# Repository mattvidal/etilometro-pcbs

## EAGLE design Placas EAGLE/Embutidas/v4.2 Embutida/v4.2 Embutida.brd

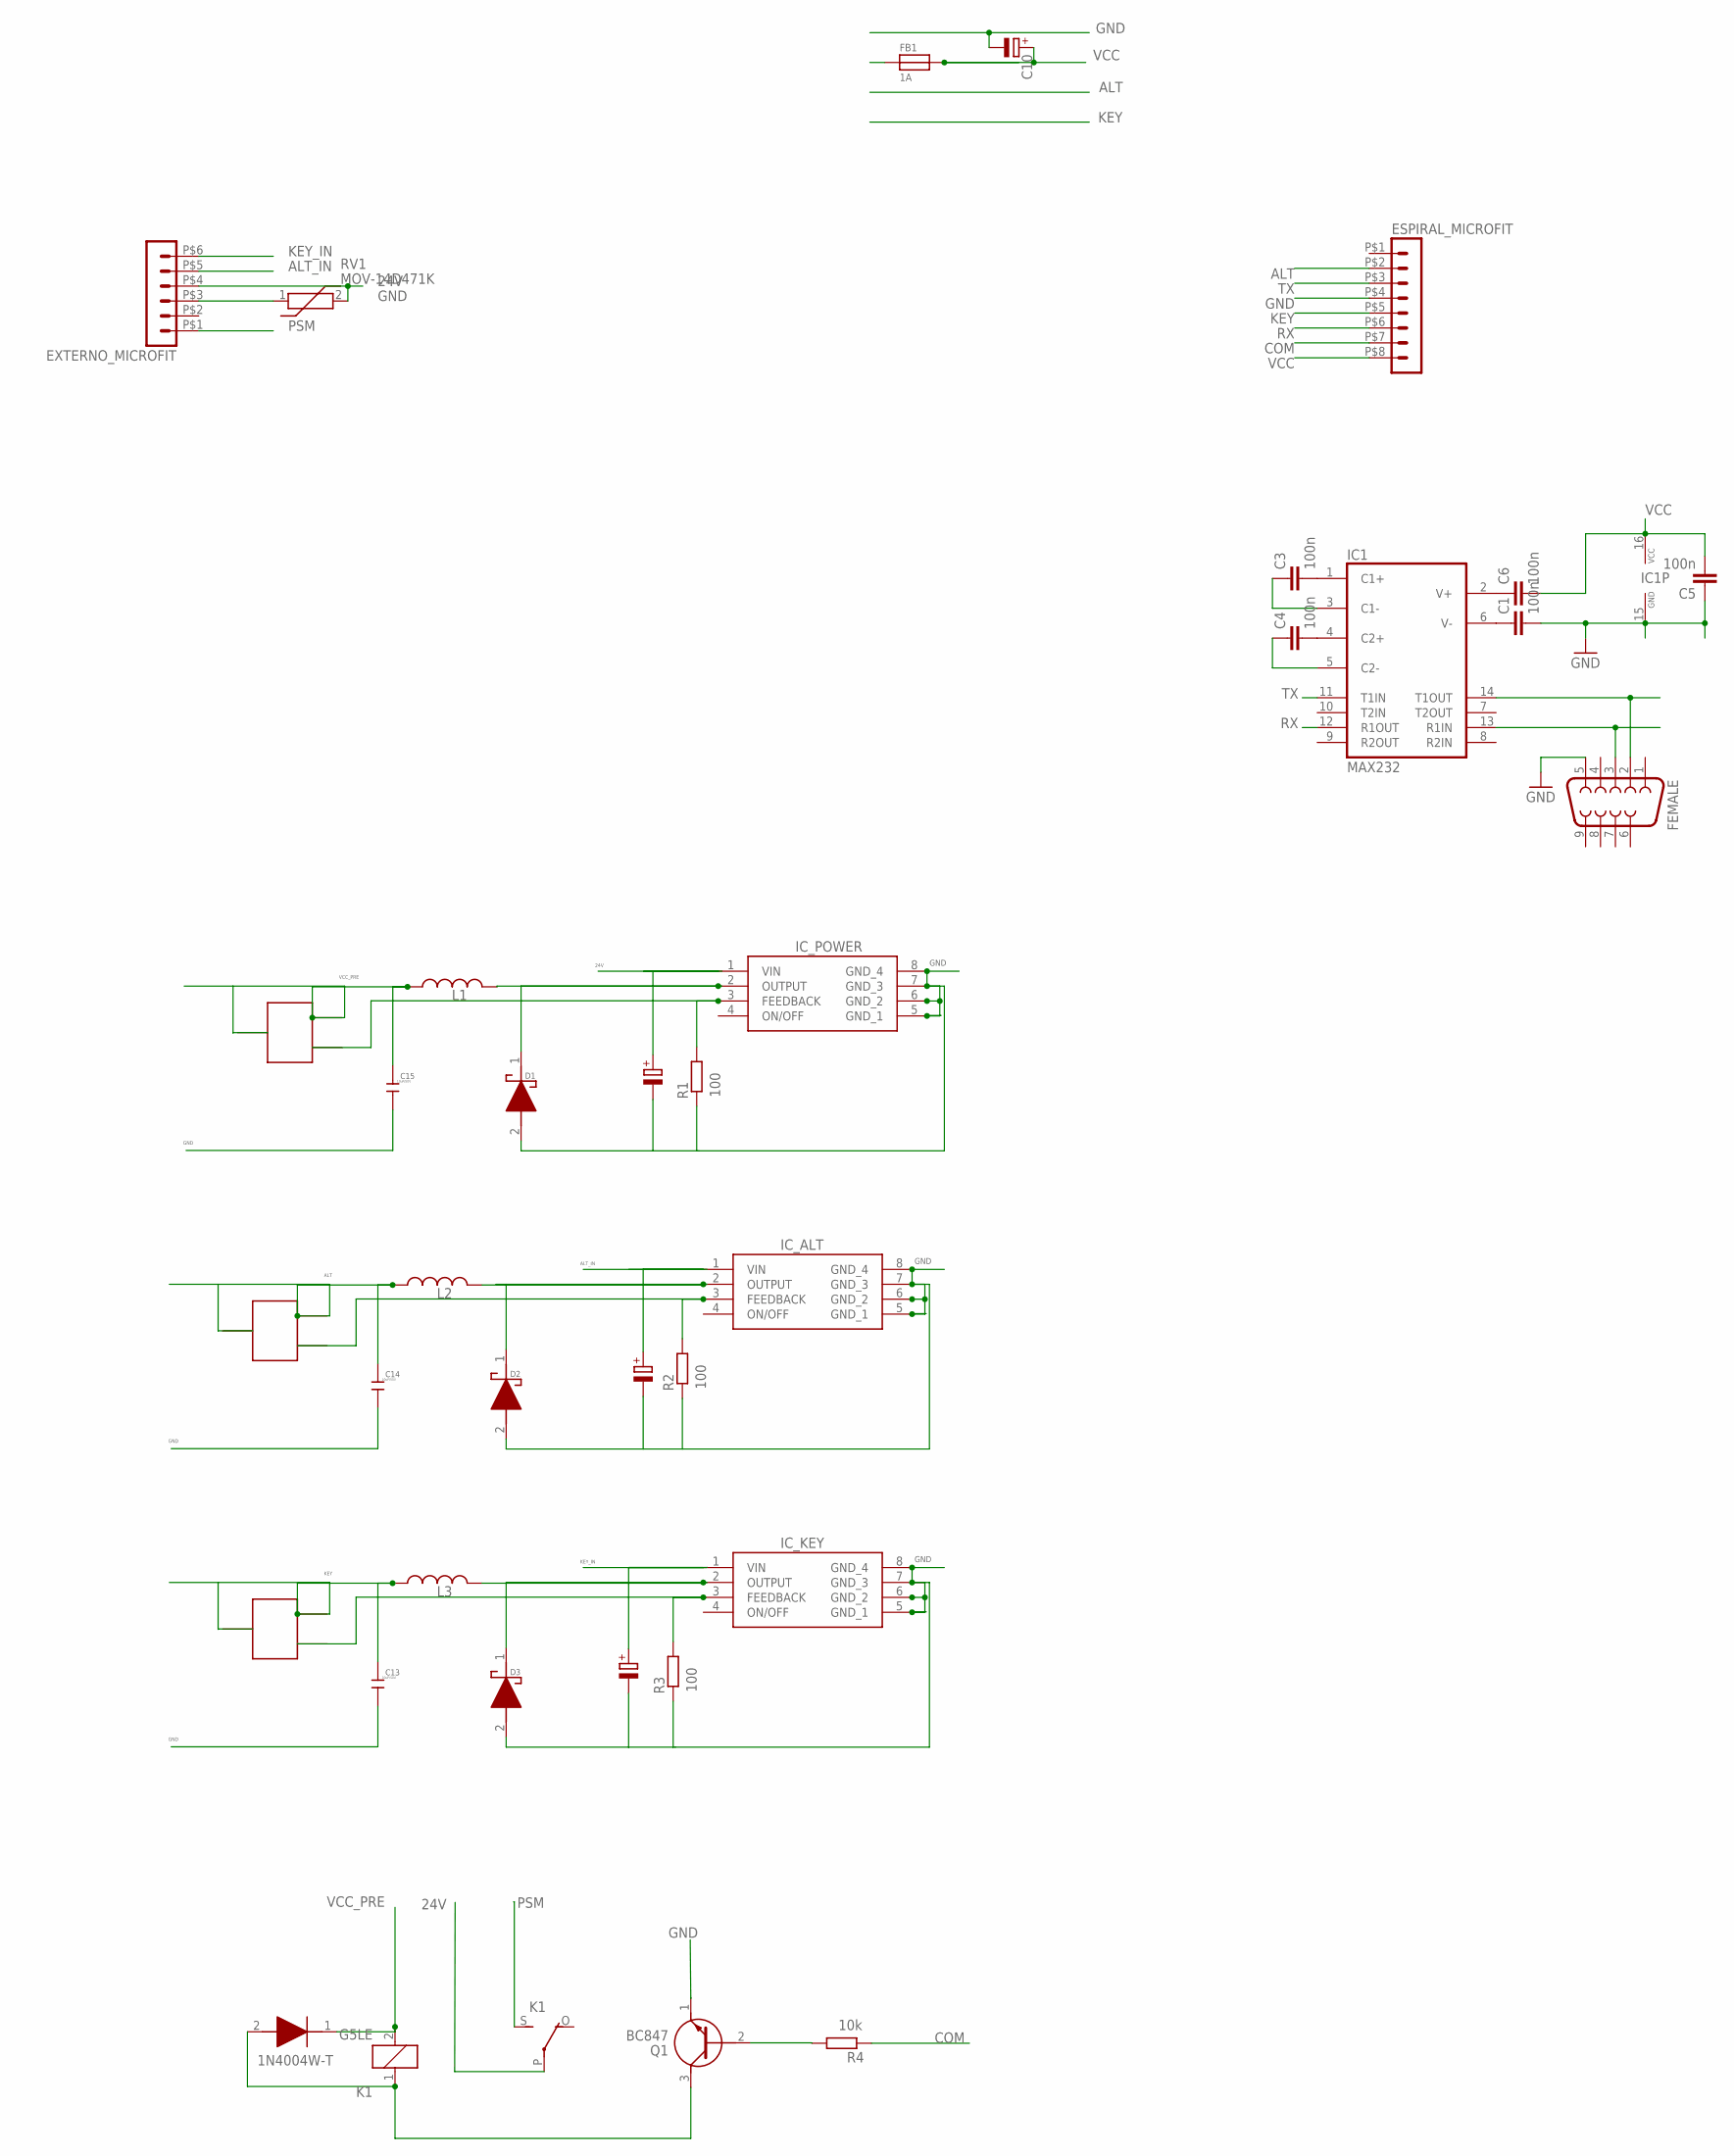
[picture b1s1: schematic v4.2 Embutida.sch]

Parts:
C1, C3, C4, C5, C6: 100n; C0805; MPN C0805C104K8RACAUTO
C2: 22uF/50v; PANASONIC_D; MPN EEH-ZA1H220P
C8, C9: 22uF/50V; PANASONIC_D; MPN EEH-ZA1H220P
C10: CPOL-EUB45181C; B45181C
C13, C14, C15: 10uF/50V; C0805; MPN C2012X5R1H106K125AC
D1, D2, D3: 1N5819HW1-7-F; SODFL3518X115N; MPN 1N5822 SS34
D5: 1N4004W-T; SODFL3818X130N
ESPIRAL_MICROFIT: HEADER_POS8_43045-0800; 43045-0800; MPN 43045-0800
EXTERNO_MICROFIT: HEADER_POS6_43045-0600; 43045-0600; MPN 43045-0600
FB1: 1A; 0805; MPN BLM21AG121SN1D
FEMALE: F09H; MPN FEMALE DR9
IC1: MAX232; SO16; MPN MAX3232CSE+
IC_ALT: XL1509-3.3E1; SOIC127P600X175-8N; MPN XL1509-ADJE1
IC_KEY: XL1509-3.3E1; SOIC127P600X175-8N; MPN XL1509-ADJE1
IC_POWER: XL1509-3.3E1; SOIC127P600X175-8N; MPN XL1509-ADJE1
K1: G5LE
L1, L2, L3: 47uH; SDE0604A-470M; MPN SDE0604A-470M
Q1: BC847
R1, R2, R3: 100; R0805; MPN RA73F2A100RBTDF
R4: 10k; R0805; MPN RA73F2A100RBTDF
RV1: MOV-14D471K; MOV14D471K
T1, T2, T3: TRIMPOT 10K; TRIMPOT; MPN EVM3ESX50B14

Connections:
24V: C2.+, EXTERNO_MICROFIT.P$4 (4), IC_POWER.1 (VIN), K1.P, RV1.2
ALT: C14.2, ESPIRAL_MICROFIT.P$2 (2), L2.1, T2.VCC1, T2.VCC2
ALT_IN: C8.+, EXTERNO_MICROFIT.P$5 (5), IC_ALT.1 (VIN)
COM: ESPIRAL_MICROFIT.P$7 (7), R4.1
GND: C1.2, C2.-, C5.1, C8.-, C9.-, C10.-, C13.1, C14.1, C15.1, D1.2 (A), D2.2 (A), D3.2 (A), ESPIRAL_MICROFIT.P$4 (4), EXTERNO_MICROFIT.P$3 (3), FEMALE.5, IC1.15 (GND), IC_ALT.5 (GND_1), IC_ALT.6 (GND_2), IC_ALT.7 (GND_3), IC_ALT.8 (GND_4), IC_KEY.5 (GND_1), IC_KEY.6 (GND_2), IC_KEY.7 (GND_3), IC_KEY.8 (GND_4), IC_POWER.5 (GND_1), IC_POWER.6 (GND_2), IC_POWER.7 (GND_3), IC_POWER.8 (GND_4), Q1.1 (E), R1.1, R2.1, R3.1, RV1.1
KEY: C13.2, ESPIRAL_MICROFIT.P$5 (5), L3.1, T3.VCC1, T3.VCC2
KEY_IN: C9.+, EXTERNO_MICROFIT.P$6 (6), IC_KEY.1 (VIN)
unnamed: D1.1 (K), IC_POWER.2 (OUTPUT), L1.2
unnamed: D2.1 (K), IC_ALT.2 (OUTPUT), L2.2
unnamed: IC_ALT.3 (FEEDBACK), R2.2, T2.OUT
unnamed: D3.1 (K), IC_KEY.2 (OUTPUT), L3.2
unnamed: IC_KEY.3 (FEEDBACK), R3.2, T3.OUT
unnamed: D5.2 (A), K1.1, Q1.3 (C)
unnamed: IC_POWER.3 (FEEDBACK), R1.2, T1.OUT
unnamed: Q1.2 (B), R4.2
unnamed: C3.2, IC1.1 (C1+)
unnamed: C4.2, IC1.4 (C2+)
unnamed: C3.1, IC1.3 (C1-)
unnamed: C4.1, IC1.5 (C2-)
unnamed: C6.1, IC1.2 (V+)
unnamed: C1.1, IC1.6 (V-)
unnamed: FEMALE.2, IC1.14 (T1OUT)
unnamed: FEMALE.3, IC1.13 (R1IN)
PSM: EXTERNO_MICROFIT.P$1 (1), K1.S
RX: ESPIRAL_MICROFIT.P$6 (6), IC1.12 (R1OUT)
TX: ESPIRAL_MICROFIT.P$3 (3), IC1.11 (T1IN)
VCC: C5.2, C6.2, C10.+, ESPIRAL_MICROFIT.P$8 (8), FB1.2, IC1.16 (VCC)
VCC_PRE: C15.2, D5.1 (K), FB1.1, K1.2, L1.1, T1.VCC1, T1.VCC2

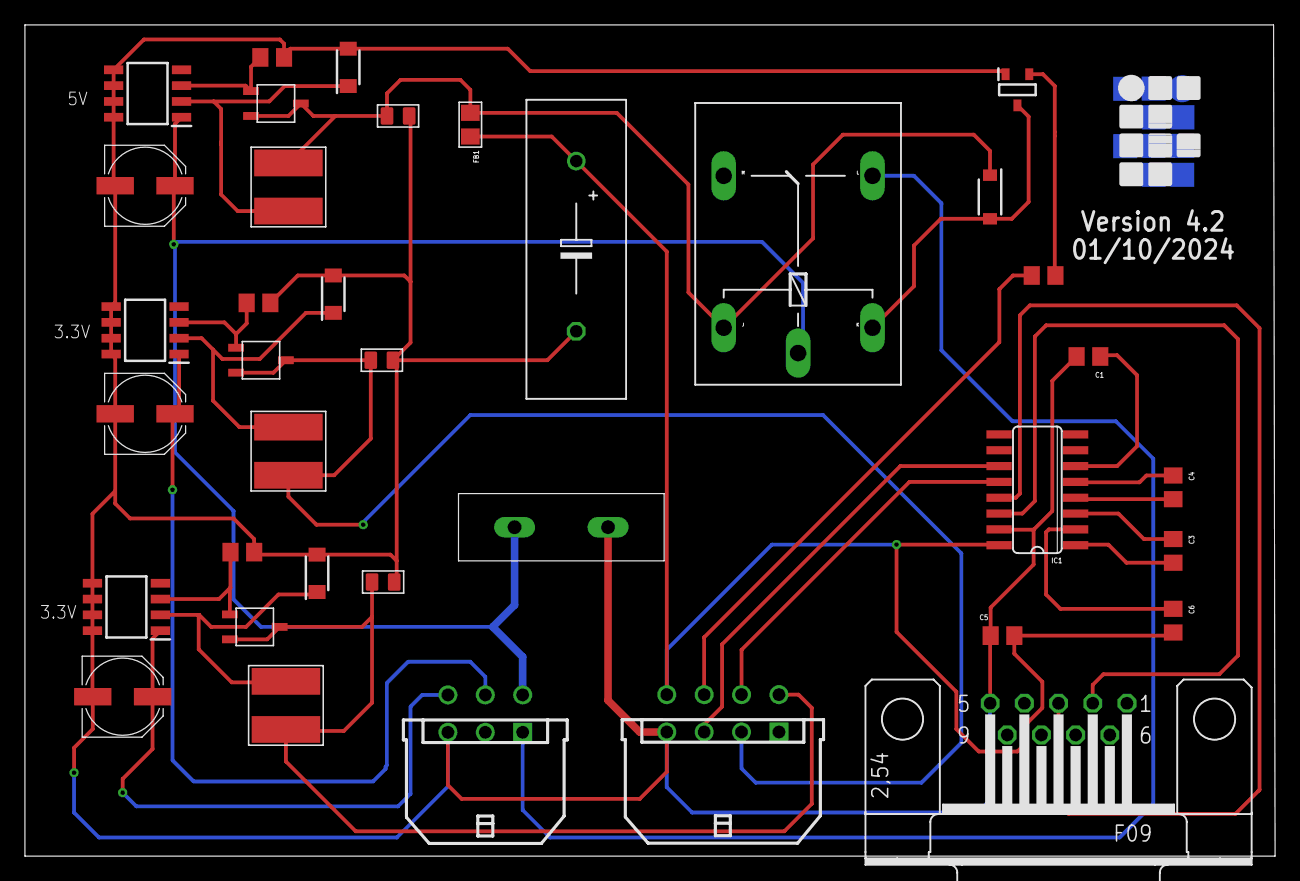
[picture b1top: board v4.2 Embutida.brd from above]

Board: 2 copper layers, 100.3 x 66.7 mm, 37 parts (0 on the bottom side), 28 nets.

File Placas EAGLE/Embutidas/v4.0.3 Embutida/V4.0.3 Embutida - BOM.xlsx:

Part | Value | MPN
C1 | 100n | C0805C104K8RACAUTO
C2 | 22uF/50v | EEH-ZA1H220P
C3 | 100n | C0805C104K8RACAUTO
C4 | 100n | C0805C104K8RACAUTO
C5 | 100n | C0805C104K8RACAUTO
C6 | 100n | C0805C104K8RACAUTO
C8 | 22uF/50V | EEH-ZA1H220P
C9 | 22uF/50V | EEH-ZA1H220P
C10 | 2200 uF | EEV-FK1A222Q
C13 | 10uF/50V | C2012X5R1H106K125AC
C14 | 10uF/50V | C2012X5R1H106K125AC
C15 | 10uF/50V | C2012X5R1H106K125AC
D1 | 1N5819HW1-7-F | 1N5822 SS34
D2 | 1N5819HW1-7-F | 1N5822 SS34
D3 | 1N5819HW1-7-F | 1N5822 SS34
D5 |  | 1N4004W-T
ESPIRAL_MICROFIT |  | 43045-0800
EXTERNO_MICROFIT |  | 43045-0600
FB1 | 1A | BLM21AG121SN1D
FEMALE |  | FEMALE DR9
IC1 | MAX232 | MAX3232CSE+
IC_ALT | XL1509-3.3E1 | XL1509-ADJE1
IC_KEY | XL1509-3.3E1 | XL1509-ADJE1
IC_POWER | XL1509-3.3E1 | XL1509-ADJE1
K1 |  | G5LE
L1 | 47uH | SDE0604A-470M
L2 | 47uH | SDE0604A-470M
L3 | 47uH | SDE0604A-470M
Q1 |  | BC847
R1 | 100 | RA73F2A100RBTDF
R2 | 100 | RA73F2A100RBTDF
R3 | 100 | RA73F2A100RBTDF
R4 | 10k | RA73F2A100RBTDF
T1 | TRIMPOT 10K | EVM3ESX50B14
T2 | TRIMPOT 10K | EVM3ESX50B14
T3 | TRIMPOT 10K | EVM3ESX50B14

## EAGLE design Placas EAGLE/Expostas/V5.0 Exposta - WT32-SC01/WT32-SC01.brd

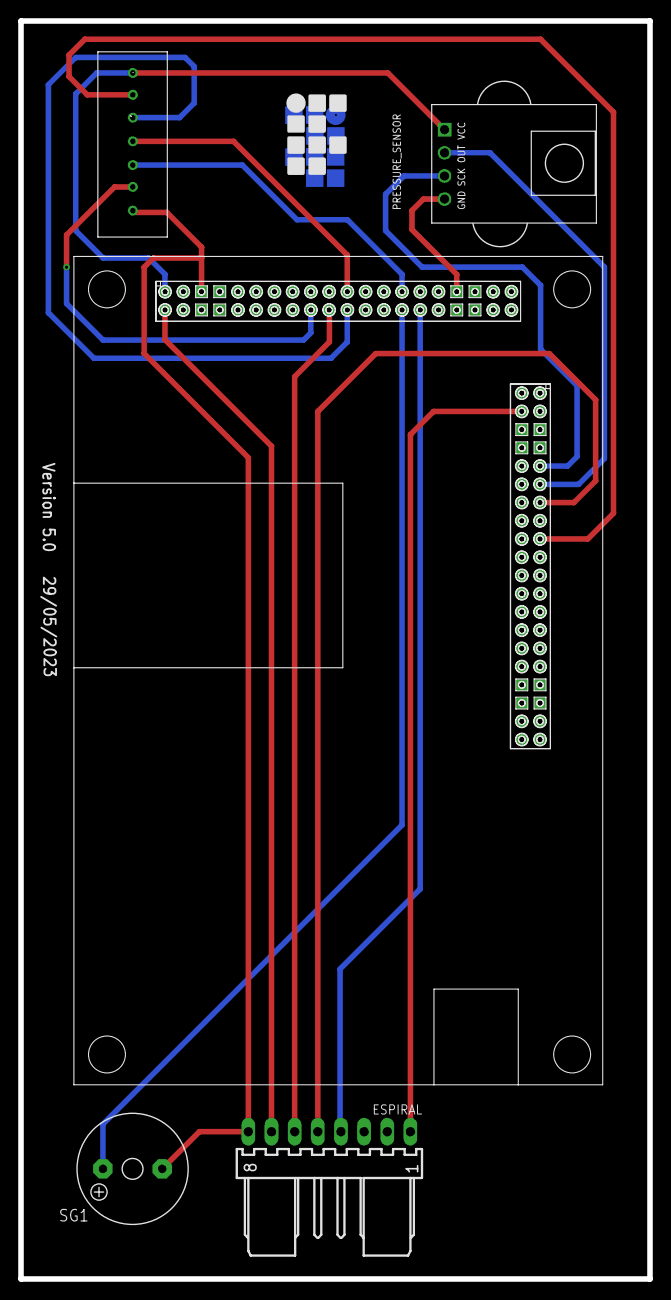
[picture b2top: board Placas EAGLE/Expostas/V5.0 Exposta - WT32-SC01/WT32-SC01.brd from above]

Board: 2 copper layers, 69.0 x 138.0 mm, 5 parts (0 on the bottom side), 14 nets.

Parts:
ESPIRAL: Espiral; 7395-08
PRESSURE_SENSOR: PRESSURE_SENSORWITH_SMDPADS&THROUGHHOLES; MPS20N0040D
SG1: F/QMX
U$1: SENSOR
U$2: WT32_SC01; WT32

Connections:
3V3: ESPIRAL.1, U$2.3V3_3, U$2.3V3_4, U$2.3V3_5, U$2.3V3_6
5V: ESPIRAL.7, PRESSURE_SENSOR.VCC, U$1.VCC, U$2.5V, U$2.5V_2, U$2.5V_3, U$2.5V_4, U$2.5V_5, U$2.5V_6, U$2.5V_7, U$2.5V_8
GND: ESPIRAL.8, PRESSURE_SENSOR.GND, SG1.-, U$1.GND, U$2.GND, U$2.GND_2, U$2.GND_3, U$2.GND_4, U$2.GND_5, U$2.GND_6, U$2.GND_7, U$2.GND_8, U$2.GND_9, U$2.GND_10, U$2.GND_11, U$2.GND_12, U$2.GND_13, U$2.GND_14, U$2.P$7, U$2.P$8
IO0: U$1.HEAT, U$2.IO0, U$2.IO0_2
IO22: U$1.SCL, U$2.IO22, U$2.IO22_2
IO32: PRESSURE_SENSOR.OUT, U$2.IO32, U$2.IO32_2
IO33: PRESSURE_SENSOR.SCK, U$2.IO33, U$2.IO33_2
unnamed: ESPIRAL.6, U$2.IO23_2
unnamed: ESPIRAL.4, U$2.IO2_2
unnamed: U$1.A_OUT, U$2.IO34_2
unnamed: U$1.SDA, U$2.IO21_2
unnamed: U$1.WR, U$2.IO12
unnamed: SG1.+, U$2.IO15_2
unnamed: ESPIRAL.5, U$2.IO27

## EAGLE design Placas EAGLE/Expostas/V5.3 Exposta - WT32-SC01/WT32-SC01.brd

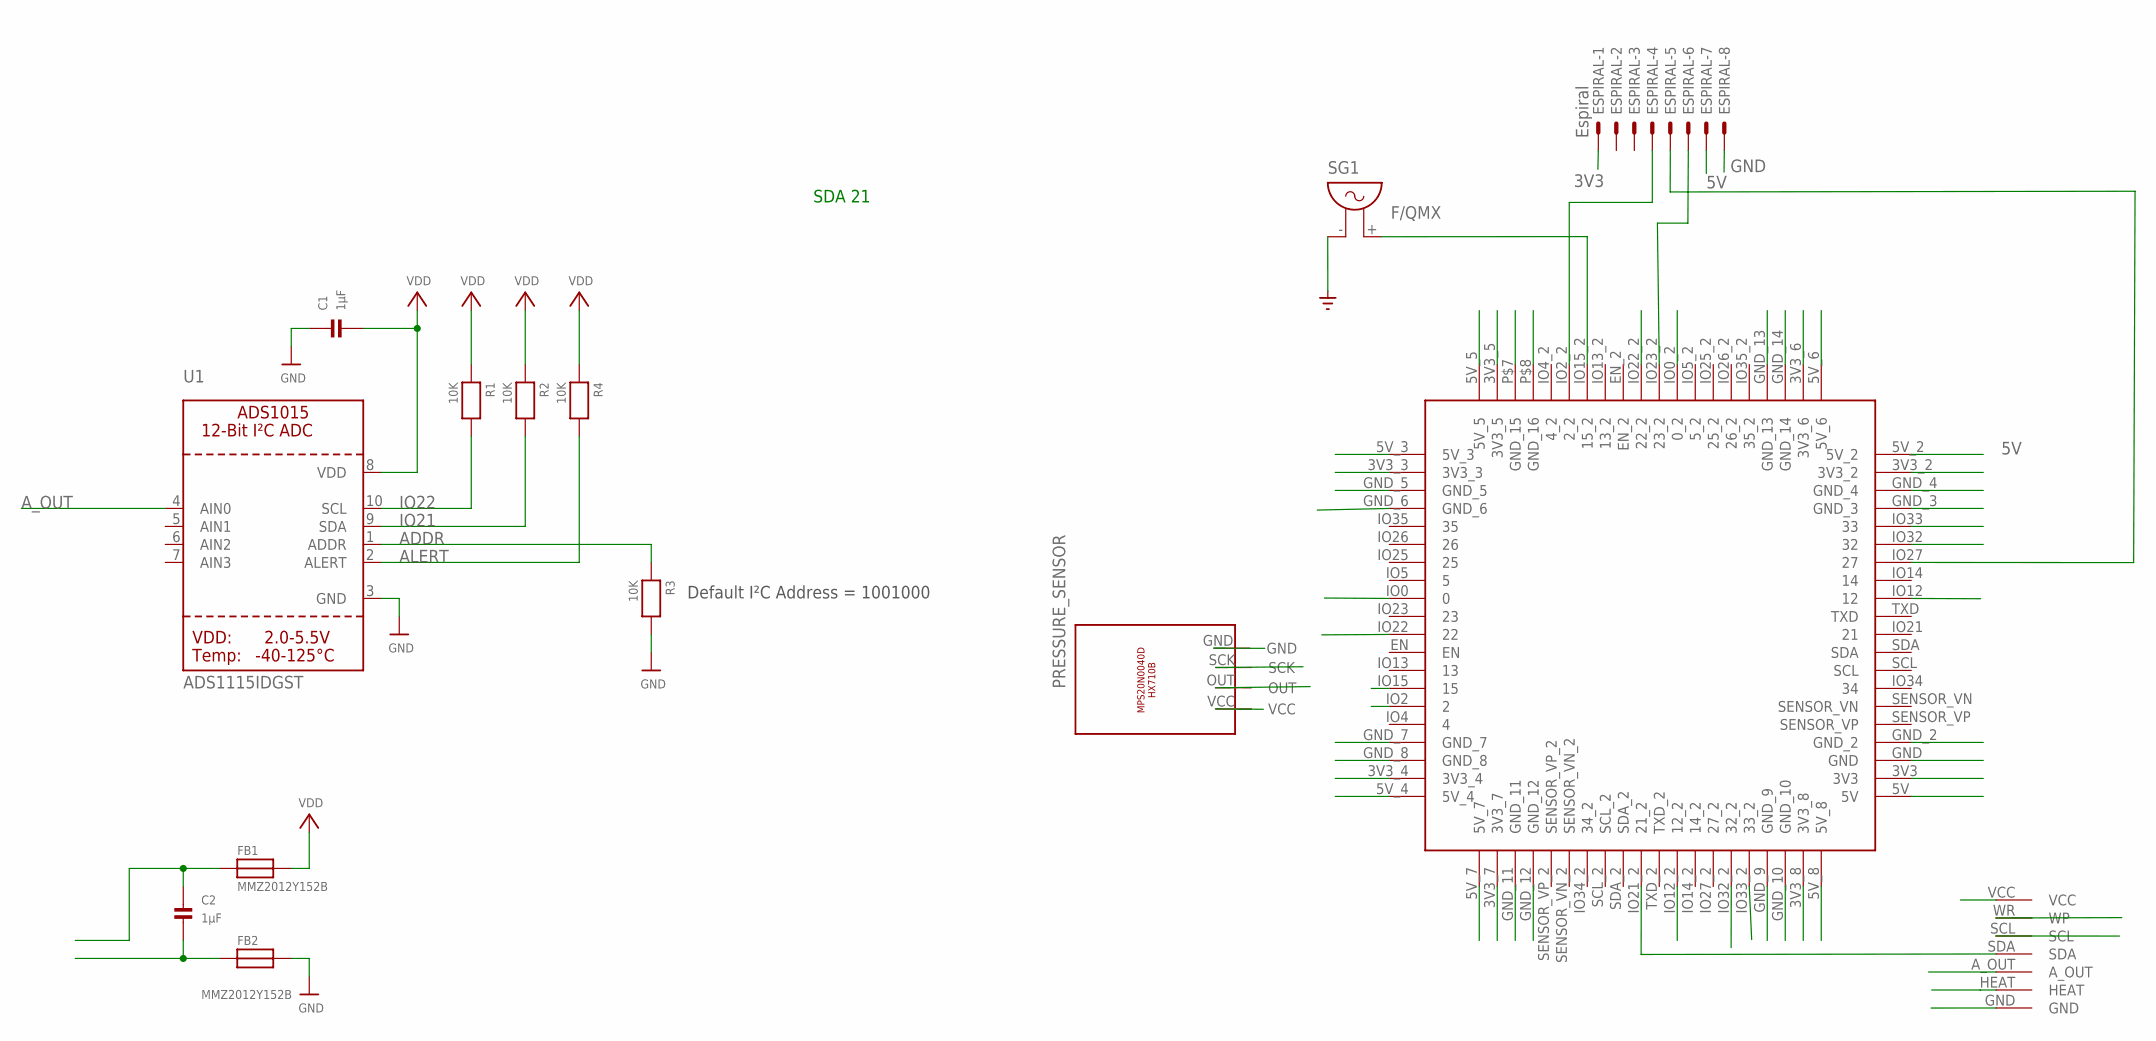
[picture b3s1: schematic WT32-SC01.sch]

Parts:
C1, C2: 1µF; 0805
ESPIRAL: Espiral; 7395-08
FB1, FB2: MMZ2012Y152B; 0805
PRESSURE_SENSOR: PRESSURE_SENSORWITH_SMDPADS&THROUGHHOLES; MPS20N0040D
R1, R2, R3, R4: 10K; 0805
SG1: F/QMX
U1: ADS1115IDGST; MSOP10
U$1: SENSOR
U$2: WT32_SC01; WT32

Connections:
3V3: ESPIRAL.1, U$2.3V3, U$2.3V3_2, U$2.3V3_3, U$2.3V3_4, U$2.3V3_5, U$2.3V3_6
5V: ESPIRAL.7, FB1.2, PRESSURE_SENSOR.VCC, U$1.VCC, U$2.5V, U$2.5V_2, U$2.5V_3, U$2.5V_4, U$2.5V_5, U$2.5V_6, U$2.5V_7, U$2.5V_8
ADDR: R3.1, U1.1 (ADDR)
ALERT: R4.2, U1.2 (ALERT)
A_OUT: U1.4 (AIN0), U$1.A_OUT
GND: C1.1, ESPIRAL.8, FB2.2, PRESSURE_SENSOR.GND, R3.2, SG1.- (1), U1.3 (GND), U$1.GND, U$2.GND, U$2.GND_2, U$2.GND_3, U$2.GND_4, U$2.GND_5, U$2.GND_6, U$2.GND_7, U$2.GND_8, U$2.GND_9, U$2.GND_10, U$2.GND_11, U$2.GND_12, U$2.GND_13, U$2.GND_14, U$2.P$7 (GND_15), U$2.P$8 (GND_16)
IO0: U$1.HEAT, U$2.IO0 (0), U$2.IO0_2 (0_2)
IO2: ESPIRAL.4, U$2.IO2 (2), U$2.IO2_2 (2_2)
IO12: U$1.WR (WP), U$2.IO12 (12), U$2.IO12_2 (12_2)
IO15: SG1.+ (2), U$2.IO15 (15), U$2.IO15_2 (15_2)
IO21: R2.2, U1.9 (SDA), U$1.SDA, U$2.IO21_2 (21_2)
IO22: R1.2, U1.10 (SCL), U$1.SCL, U$2.IO22 (22), U$2.IO22_2 (22_2)
IO32: PRESSURE_SENSOR.OUT, U$2.IO32 (32), U$2.IO32_2 (32_2)
IO33: PRESSURE_SENSOR.SCK, U$2.IO33 (33), U$2.IO33_2 (33_2)
unnamed: ESPIRAL.6, U$2.IO23_2 (23_2)
unnamed: C2.2, FB2.1
unnamed: C2.1, FB1.1
unnamed: ESPIRAL.5, U$2.IO27 (27)
VDD: C1.2, R1.1, R2.1, R4.1, U1.8 (VDD)

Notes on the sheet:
Default I²C Address = 1001000
SDA 21

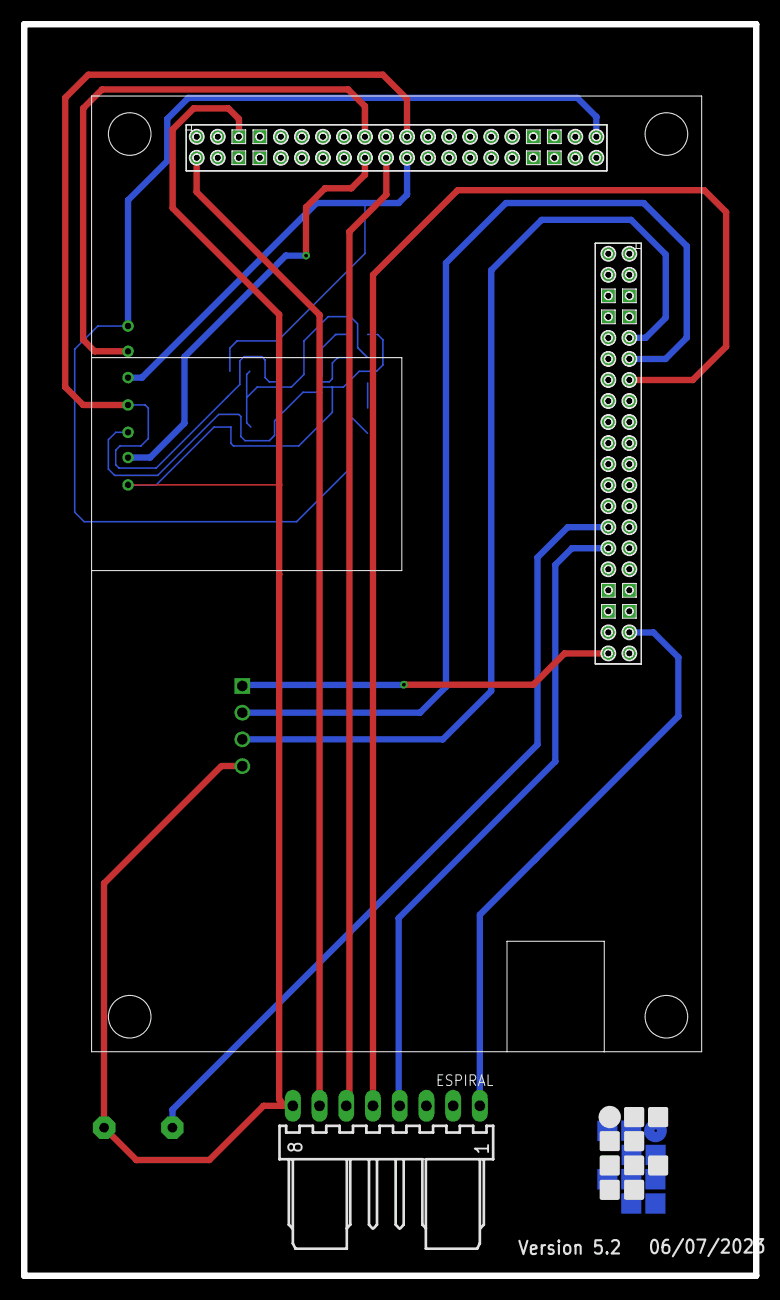
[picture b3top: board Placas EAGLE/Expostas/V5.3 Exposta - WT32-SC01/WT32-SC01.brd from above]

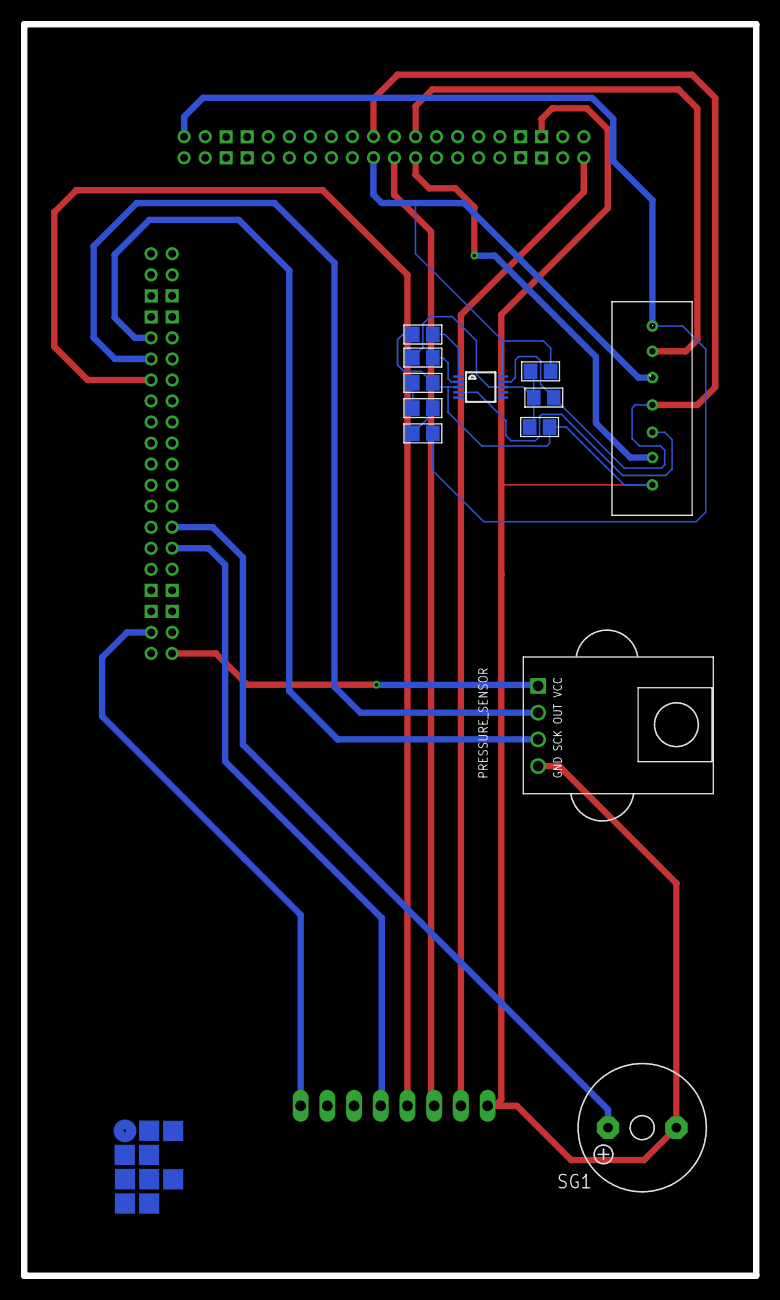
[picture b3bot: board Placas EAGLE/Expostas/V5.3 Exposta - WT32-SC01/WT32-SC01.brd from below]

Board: 2 copper layers, 69.6 x 119.0 mm, 14 parts (12 on the bottom side), 19 nets.

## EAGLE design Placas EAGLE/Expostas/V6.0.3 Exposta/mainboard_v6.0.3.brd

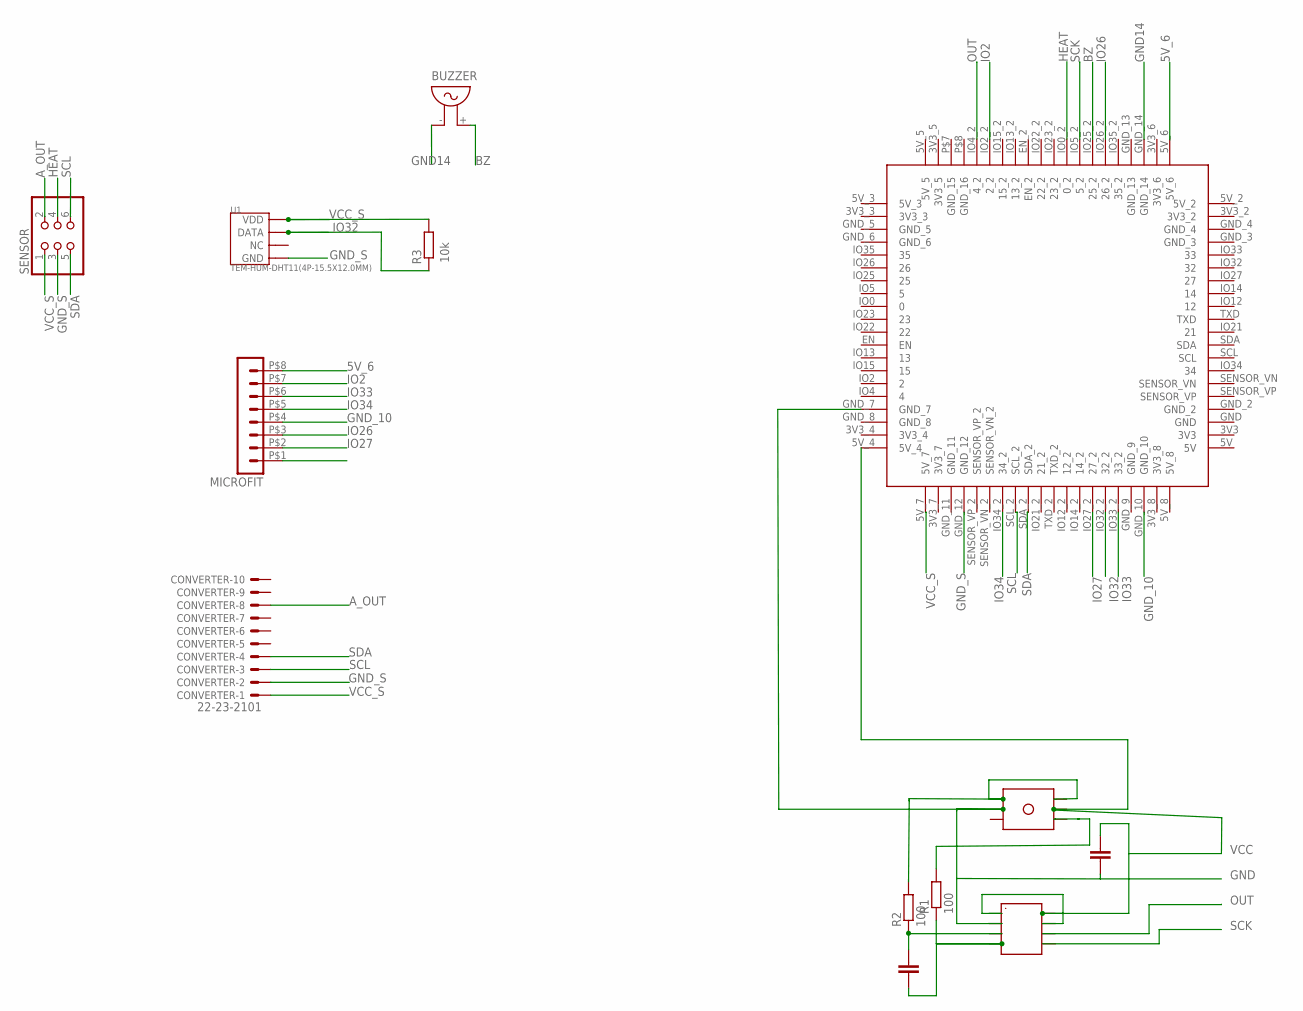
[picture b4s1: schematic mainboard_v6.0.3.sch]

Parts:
BUZZER: F/QMX
C1, C2: 100n; C0805
CONVERTER: 22-23-2101
MICROFIT: HEADER_POS8_43045-0800; 43045-0800
R1, R2: 100; R0805
R3: 10k; R0805
SENSOR: PINHD-2X3; 2X03
U1: TEM-HUM-DHT11(4P-15.5X12.0MM); SNR4-2.54-15.5X12.0X5.5MM
U$1: WT32_SC01WT32_D; WT32_DUPLICATED
U$2: HX710B; HX710B_SMD
U$3: PRESSUREPRESSURE_PTH; PRESSURE_PTH

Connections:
5V_6: MICROFIT.P$8 (8), U$1.5V_6
A_OUT: CONVERTER.8, SENSOR.2
BZ: BUZZER.+ (2), U$1.IO25_2 (25_2)
GND: C2.2, U$1.GND_7, U$2.AGND, U$3.2
GND14: BUZZER.- (1), U$1.GND_14
GND_10: MICROFIT.P$4 (4), U$1.GND_10
GND_S: CONVERTER.2, SENSOR.3, U1.4 (GND), U$1.GND_12
HEAT: SENSOR.4, U$1.IO0_2 (0_2)
IO2: MICROFIT.P$7 (7), U$1.IO2_2 (2_2)
IO26: MICROFIT.P$3 (3), U$1.IO26_2 (26_2)
IO27: MICROFIT.P$2 (2), U$1.IO27_2 (27_2)
IO32: R3.1, U1.2 (DATA), U$1.IO32_2 (32_2)
IO33: MICROFIT.P$6 (6), U$1.IO33_2 (33_2)
IO34: MICROFIT.P$5 (5), U$1.IO34_2 (34_2)
unnamed: C1.2, R2.1, U$2.INN
unnamed: C1.1, R1.1, U$2.INP
unnamed: R1.2, U$3.4
unnamed: R2.2, U$3.1, U$3.6
OUT: U$1.IO4_2 (4_2), U$2.DOUT
SCK: U$1.IO5_2 (5_2), U$2.SCK
SCL: CONVERTER.3, SENSOR.6, U$1.SCL_2
SDA: CONVERTER.4, SENSOR.5, U$1.SDA_2
VCC: C2.1, U$1.5V_4, U$2.AVDD, U$2.DVDD, U$2.VREF, U$3.5
VCC_S: CONVERTER.1, R3.2, SENSOR.1, U1.1 (VDD), U$1.5V_7

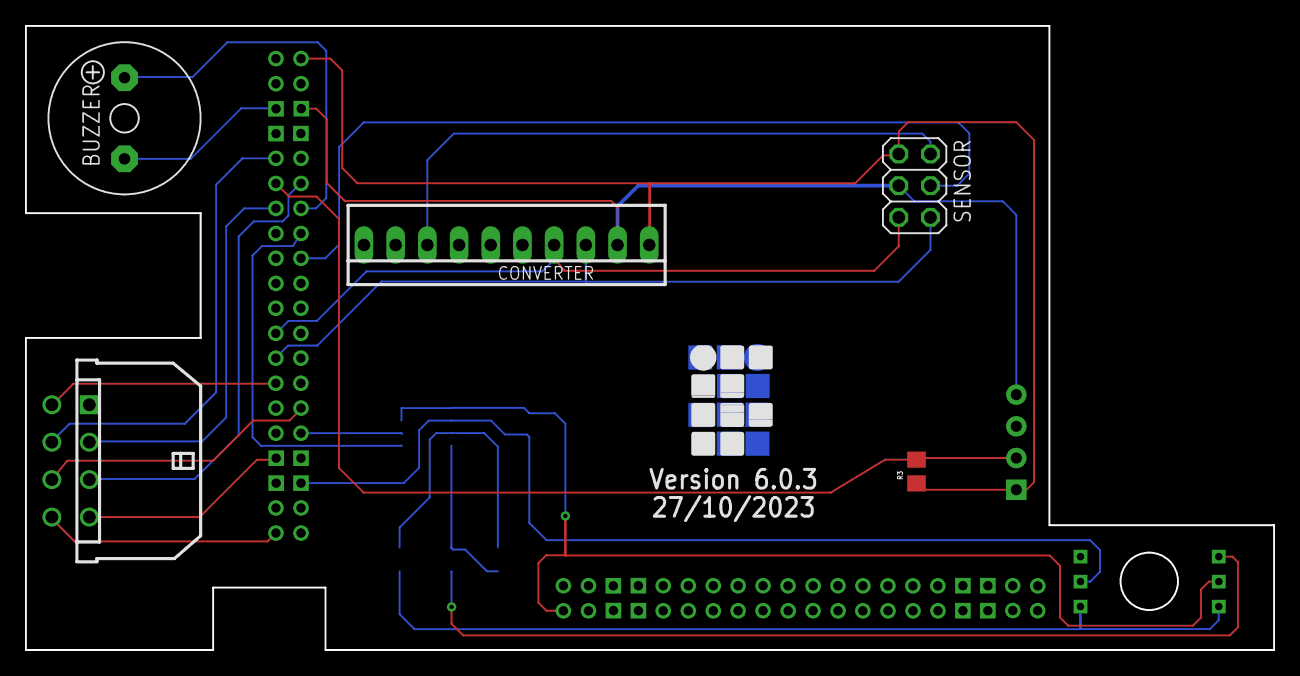
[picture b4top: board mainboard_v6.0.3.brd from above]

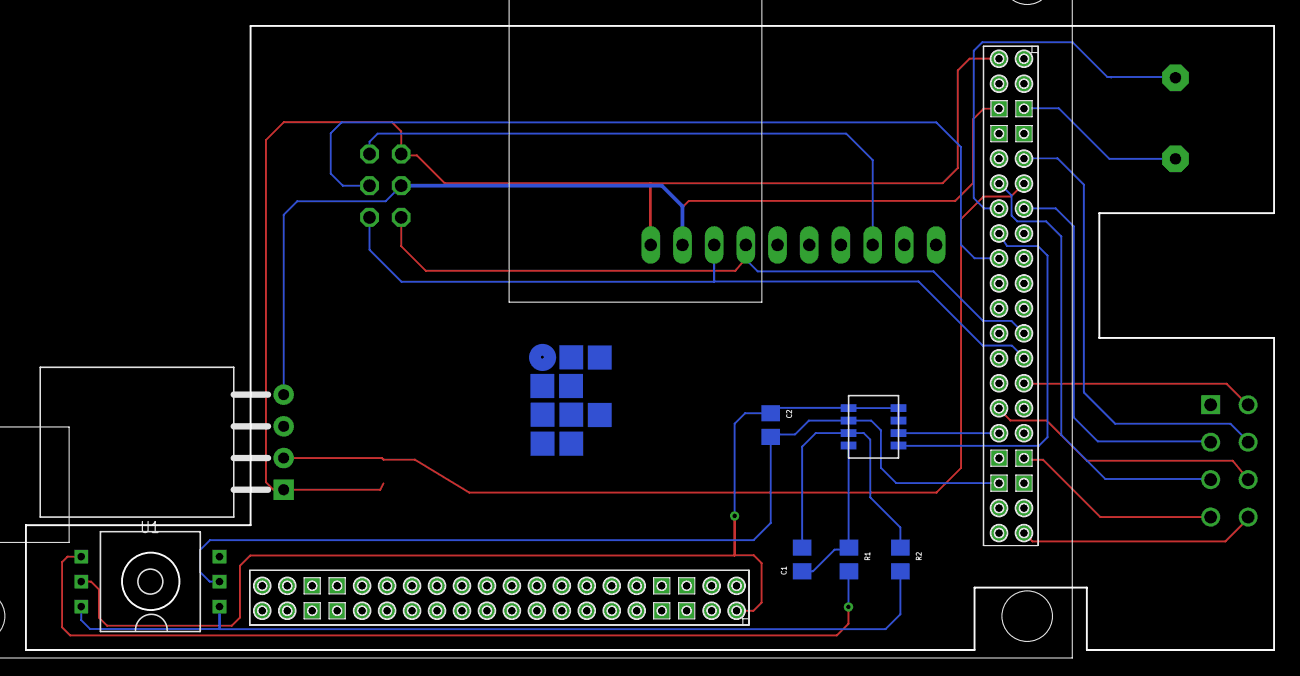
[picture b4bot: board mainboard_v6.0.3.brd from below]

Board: 2 copper layers, 100.0 x 50.0 mm, 13 parts (8 on the bottom side), 24 nets.
